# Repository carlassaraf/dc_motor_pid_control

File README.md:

# dc_motor_pid_control
Control PID para la posición de un motor de continua.

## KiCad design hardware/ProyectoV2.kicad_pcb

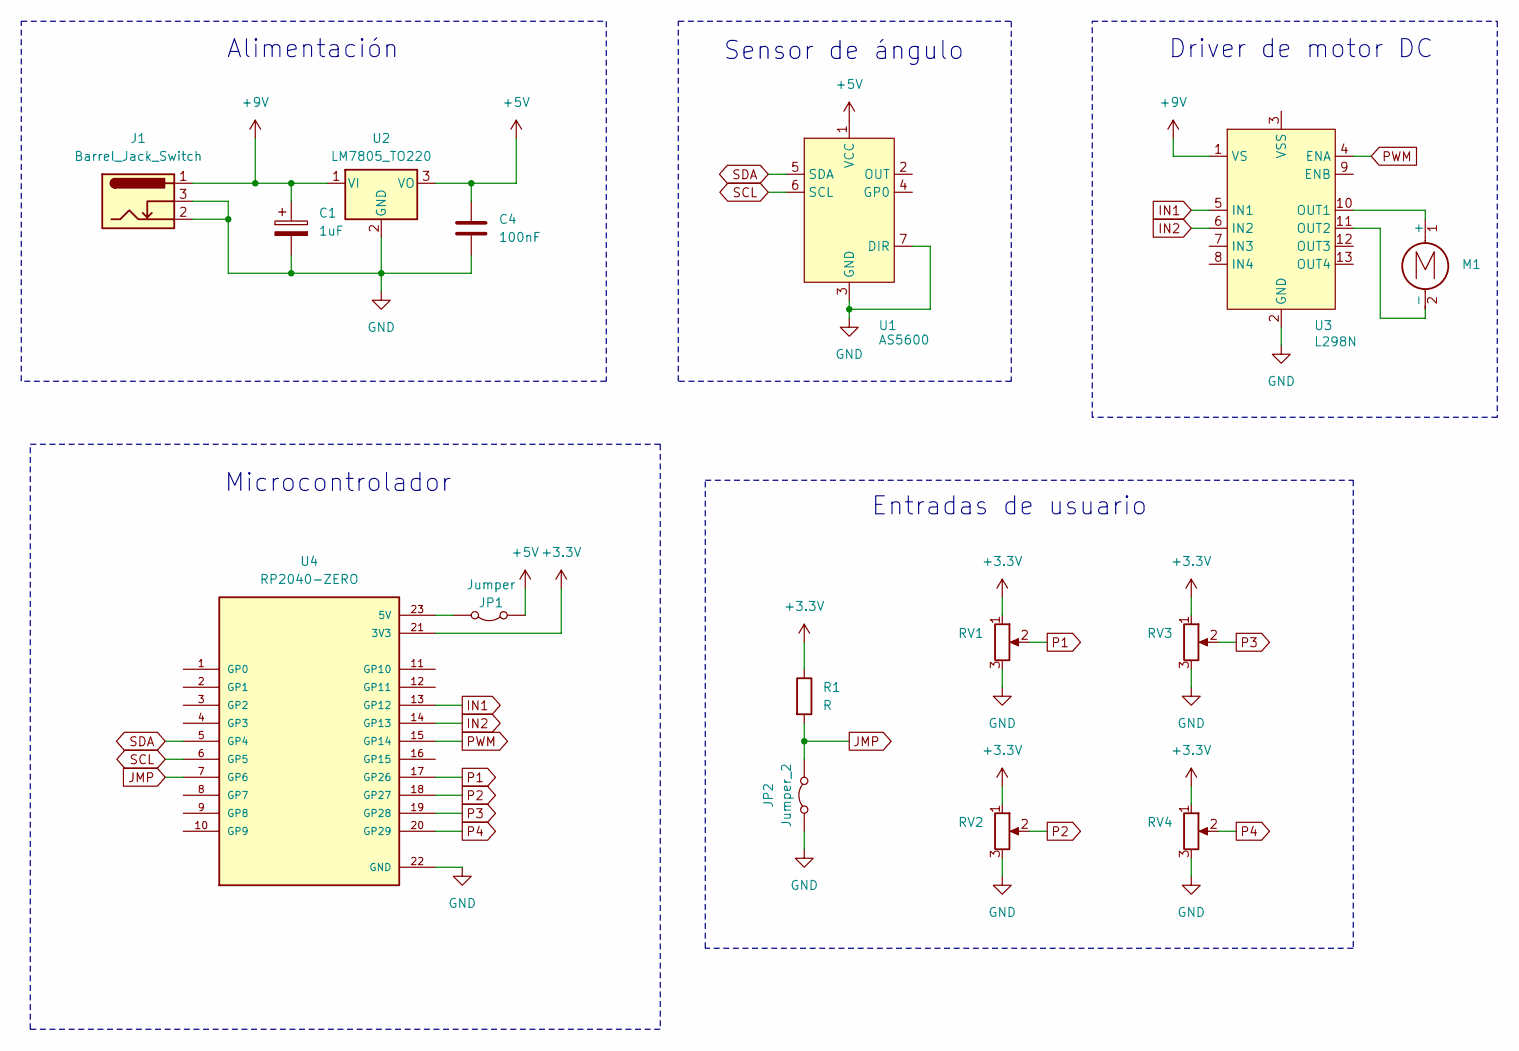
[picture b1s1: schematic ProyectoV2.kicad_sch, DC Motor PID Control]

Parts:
C1: 1uF; CP_Radial_D5.0mm_P2.50mm
C4: 100nF; C_Disc_D5.0mm_W2.5mm_P5.00mm
J1: Barrel_Jack_Switch; BarrelJack_Horizontal
JP1: Jumper; TestPoint_2Pads_Pitch2.54mm_Drill0.8mm
JP2: Jumper_2; TestPoint_2Pads_Pitch2.54mm_Drill0.8mm
M1: Motor_DC
R1: R; R_Axial_DIN0207_L6.3mm_D2.5mm_P10.16mm_Horizontal
RV1, RV2, RV3, RV4: R_Potentiometer; Potentiometer_Alps_RK163_Single_Horizontal
U1: AS5600; PinHeader_1x07_P2.54mm_Vertical
U2: LM7805_TO220; TO-220-3_Vertical
U3: L298N; PinHeader_2x07_P2.54mm_Vertical
U4: RP2040-ZERO; rp2040-zero-tht; PARTREV NA

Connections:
+3.3V: R1.1, RV1.1, RV2.1, RV3.1, RV4.1, U4.21 (3V3)
+5V: C4.1, JP1.1 (A), U1.1 (VCC), U2.3 (VO)
+9V: C1.1, J1.1, U2.1 (VI), U3.1 (VS)
GND: C1.2, C4.2, J1.2, J1.3, JP2.1 (A), RV1.3, RV2.3, RV3.3, RV4.3, U1.3 (GND), U1.7 (DIR), U2.2 (GND), U3.2 (GND), U4.22 (GND)
IN1: U3.5 (IN1), U4.13 (GP12)
IN2: U3.6 (IN2), U4.14 (GP13)
JMP: JP2.2 (B), R1.2, U4.7 (GP6)
unnamed: JP1.2 (B), U4.23 (5V)
unnamed: M1.1 (+), U3.10 (OUT1)
unnamed: M1.2 (-), U3.11 (OUT2)
P1: RV1.2, U4.17 (GP26)
P2: RV2.2, U4.18 (GP27)
P3: RV3.2, U4.19 (GP28)
P4: RV4.2, U4.20 (GP29)
PWM: U3.4 (ENA), U4.15 (GP14)
SCL: U1.6 (SCL), U4.6 (GP5)
SDA: U1.5 (SDA), U4.5 (GP4)

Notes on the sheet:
Driver de motor DC
Entradas de usuario
Microcontrolador
Sensor de ángulo
Alimentación

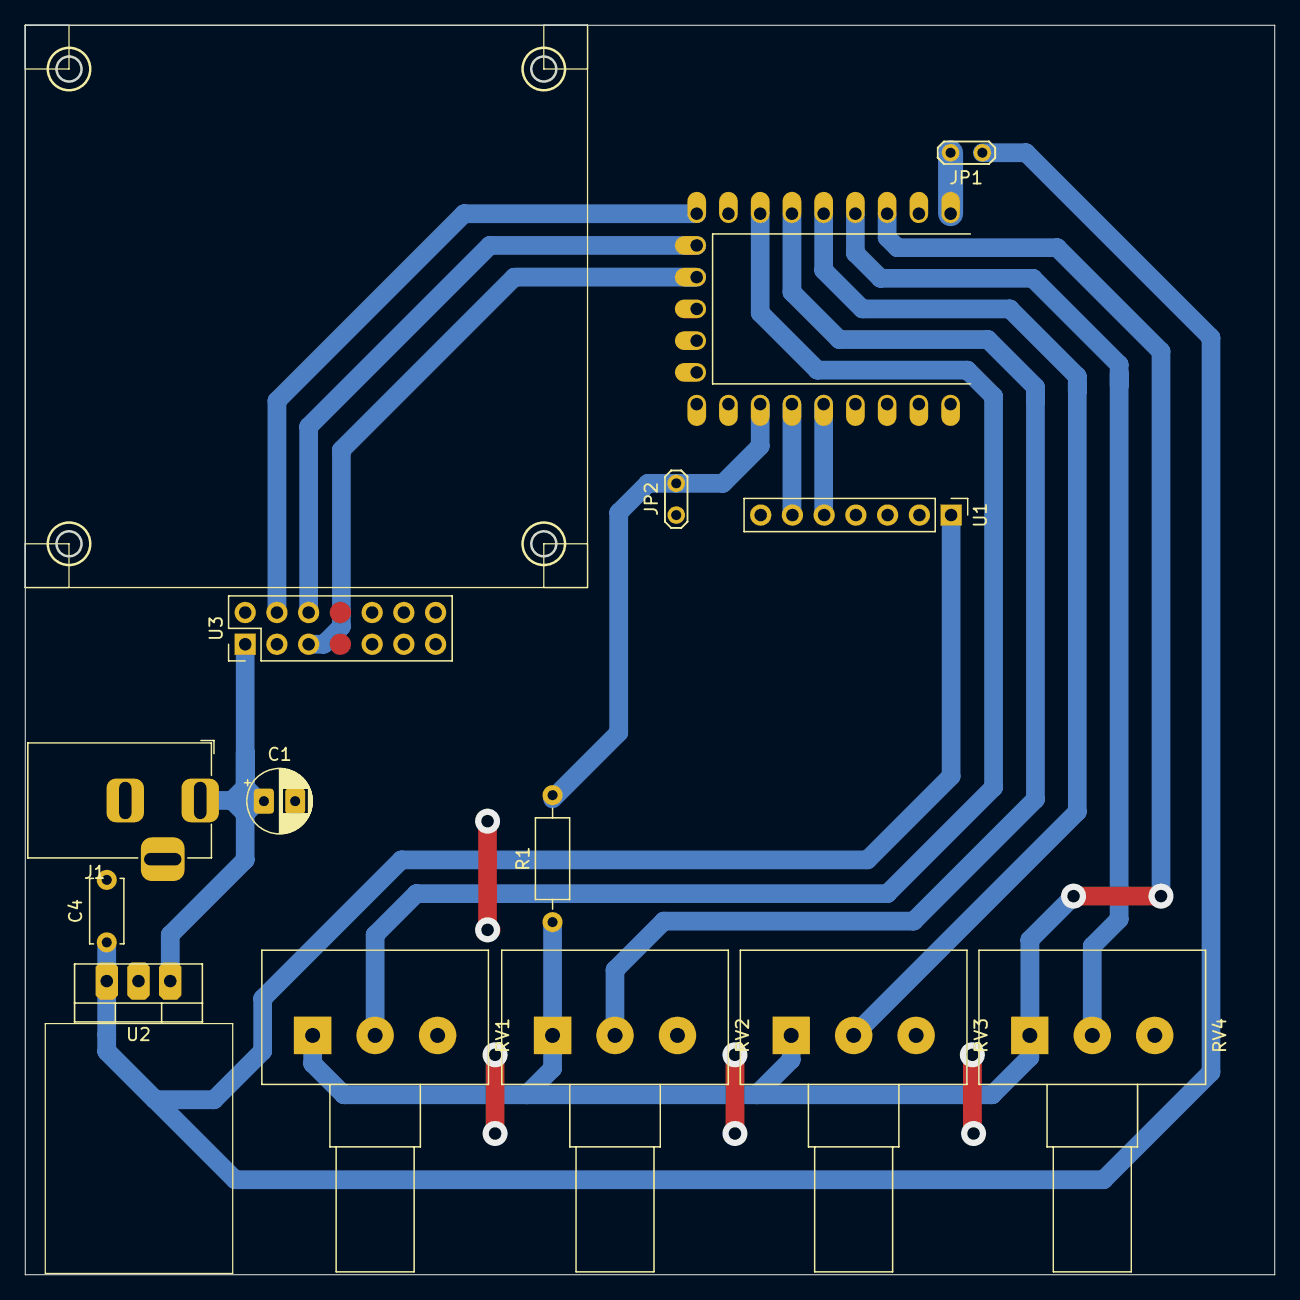
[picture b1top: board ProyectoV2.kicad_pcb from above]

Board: 2 copper layers, 100.0 x 100.0 mm, 14 parts (0 on the bottom side), 15 nets.

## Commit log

2024-06-14 chore: ignoro entorno virtual
2024-06-14 chore: paquetes necesarios
2024-06-14 feat: aplicacion
2024-06-14 feat: interfaz con dos ventanas de ploteo
2024-06-14 chore: ignoro cache
2024-06-15 feat: agrego funcion para puerto serie
2024-06-15 feat: inicializacion de conversiones
2024-06-15 feat: leo datos del serial port
2024-06-15 chore: habilito usb
2024-06-15 feat: agrego inicializacion
2024-06-15 feat: mando datos
2024-06-15 feat: muevo eje horizontal en tiempo real
2024-06-15 refactor: ajusto limites verticales
2024-06-15 docs: escribo comentarios
2024-06-15 refactor: ajusto angulos
2024-06-16 feat: agrego campos para fijar valores de pid
2024-06-16 feat: manda constantes pid por serial
2024-06-16 feat: funcion que extrae valor de json
2024-06-16 feat: lee del usb las constantes del pid
2024-06-27 chore: directorio nuevo
2025-03-05 feat: library for l298 module
2025-03-05 chore: ignore build directory
2025-03-05 chore: cmake rules
2025-03-05 chore: macros for pins used
2025-03-05 chore: basic project
2025-03-05 feat: pid library
2025-03-05 chore: delete old mcu code
2025-03-06 chore: debug optimizations
2025-03-06 fix: update previous error for proper derivative calculation
2025-03-06 fix: update dearpygui version
2025-03-06 feat: pwm data in gui
2025-03-06 feat: support plot data
2025-03-06 chore: ignore .vscode directory
2025-03-06 refactor: move reference, position and error plots on the same axis
2025-03-06 feat: get pid constants from mcu
2025-03-06 feat: add sampling time to plot data
2025-03-06 feat: sampling time comes from mcu
2025-03-06 refactor: change callback from us to ms
2025-03-06 feat: read sampling time from mcu
2025-03-06 feat: update for pid constants and sampling time available
2025-03-06 feat: magnetic encoder library
2025-03-06 feat: add sensor library reference
2025-03-06 feat: rename file and add pid constants
2025-03-06 feat: sensor, pid and motor driver initialization
2025-03-06 feat: read constants from potentiometers
2025-03-06 feat: absolute value macro
2025-03-06 feat: feed pwm with pid output
2025-04-02 fix: enable pwm function
2025-04-03 feat: add plotter handler function
2025-04-03 chore: move macros to pid source code
2025-04-04 fix: time differential in ms
2025-04-04 feat: add plotting time to data struct
2025-04-04 feat: add plotting time to input data
2025-04-18 feat: app constants and adc average
2025-04-18 feat: send ref value to plotter app
2025-04-18 feat: plotter initialization and pid constants setting
2025-04-18 feat: schematic and pcb design
2025-04-18 chore: rp2040 library
2025-04-18 chore: schematic and pcb pdf version
2025-05-01 refactor: change inputs for text
2025-05-01 refactor: change default window size
2025-07-08 feat: biblioteca de freertos
2025-07-08 feat: soporte para json en C
2025-07-08 perf: tareas de freertos
2025-07-08 perf: promedio de valores de adc
2025-07-08 chore: dependencias de freertos
2025-07-08 feat: migracion a tareas de freertos
2025-07-08 feat: potenciometros digitales en interfaz para constantes
2025-07-22 chore: move directory
2025-07-22 chore: move initialization from task to main
2025-07-22 feat: add pid constant sliders
2025-07-22 perf: update PID max values and app constants
2025-07-23 perf: adjusts to degree macro and prototipe names
2025-07-23 perf: plotting and pid timing depends on the user app implementation
2025-07-23 perf: compensates for 90 degree difference
2025-07-23 perf: pid algorithm and data plotter tasks
2025-07-23 chore: minor naming fix
2025-07-23 perf: move plottier handling and logic to separate library
2025-07-23 perf: avoid extra inclusions and added max output constants
2025-07-23 perf: added queue to share PID data between tasks
2025-07-23 chore: added plotter library
2025-08-03 feat: added support for adc constants on separate task
2025-08-03 fix: correct reference mapping
2025-08-03 feat: choose pid constants source
2025-08-03 chore: task initialization
2025-09-18 docs: instrucciones
2025-12-10 refactor: default behavior with jumper is reading PID constants
2025-12-10 fix: l298 pins and reference potentiometer reading scaling
2025-12-10 fix: scale the as5600 output
2025-12-10 perf: make sure the top four bits dont come with anything else in the top nibble
2025-12-10 fix: no need to scale with macro
2025-12-10 fix: dont need to scale differently the values to plot
